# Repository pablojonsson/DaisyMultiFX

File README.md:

# Author
Pablo Jonsson

# DaisyMultiFX
Code for a Daisy Seed development board to run guitar effects

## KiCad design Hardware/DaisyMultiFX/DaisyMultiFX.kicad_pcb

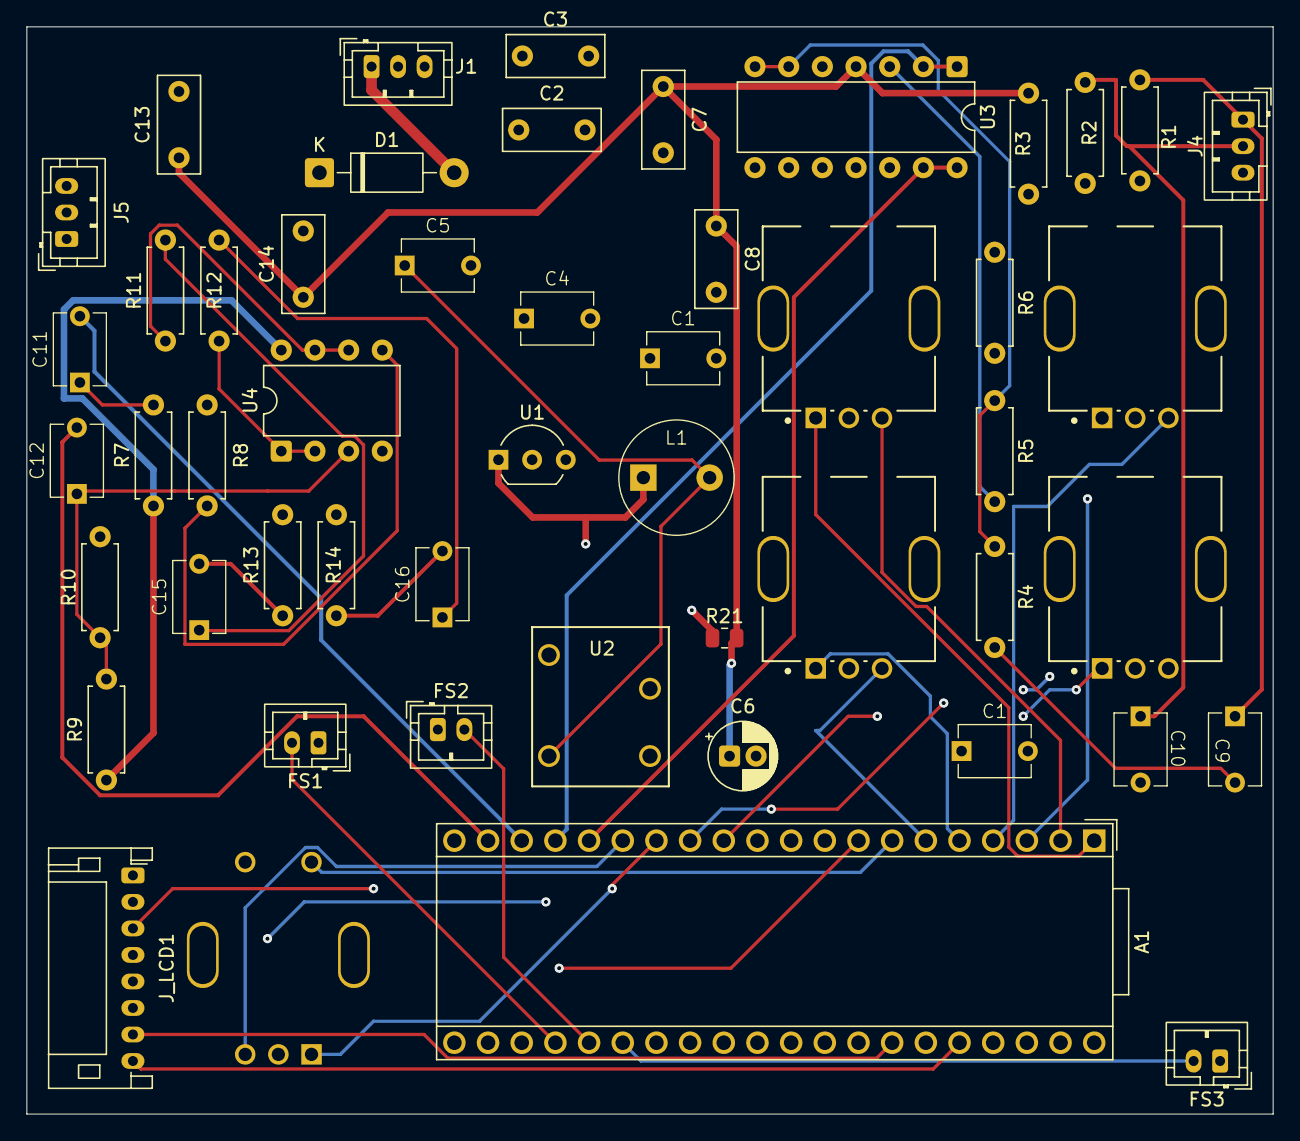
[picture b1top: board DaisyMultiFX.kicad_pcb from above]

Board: 4 copper layers, 94.0 x 82.0 mm, 51 parts (0 on the bottom side), 46 nets.

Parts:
A1: Electrosmith_Daisy_Seed_Rev4; Electrosmith_Daisy_Seed
C1, C1#2, C4, C5, C9, C10, C11, C12, C15, C16: 10UF; C_TDK_FG20_L5.5mm_T4.0mm_P5.00mm
C2, C3, C7, C8, C13, C14: 100NF; C_Rect_L7.2mm_W3.0mm_P5.00mm_FKS2_FKP2_MKS2_MKP2
C6: 22UF; CP_Radial_D5.0mm_P2.00mm
D1: 1N5817; D_DO-41_SOD81_P10.16mm_Horizontal
FS1: Foot_Switch_1; JST_PH_B2B-PH-K_1x02_P2.00mm_Vertical
FS2: Foot_Switch_2; JST_PH_B2B-PH-K_1x02_P2.00mm_Vertical
FS3: Foot_Switch_3; JST_PH_B2B-PH-K_1x02_P2.00mm_Vertical
J1: DC JACK; JST_PH_B3B-PH-K_1x03_P2.00mm_Vertical
J4: J_AUDIO_IN; JST_PH_B3B-PH-K_1x03_P2.00mm_Vertical
J5: J_AUDIO_OUT; JST_PH_B3B-PH-K_1x03_P2.00mm_Vertical
J_LCD1: WAVESHARE 2" ST7789PH2.0 8-pin; JST_PH_S8B-PH-K_1x08_P2.00mm_Horizontal
L1: 2.2uH; L_Bourns_RLB0912_D8.7mm_P5.00mm
R1, R2, R4, R5, R7, R8, R9, R10, R13, R14: 2M; R_Axial_DIN0207_L6.3mm_D2.5mm_P7.62mm_Horizontal
R3, R6: 100K; R_Axial_DIN0207_L6.3mm_D2.5mm_P7.62mm_Horizontal
R11, R12: 100R; R_Axial_DIN0207_L6.3mm_D2.5mm_P7.62mm_Horizontal
R21: DNP; R_0805_2012Metric
SW1, SW2, SW3, SW4: Encoder; Bourns-PEC11R-4220F-N0024-0-0-0
SW7: RotaryEncoder_Switch; Bourns-PEC11R-4220F-S0024-0-0-0
U1: L4931CZ50; TO-92_Inline_Wide
U2: NME0505DC; NME_DIP_MUR
U3: MCP6004; DIP-14_W7.62mm
U4: OPA2134; DIP-8_W7.62mm

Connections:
+3.3V: A1.38 (3V3_D), J_LCD1.1
+5V: C4.1, L1.1, R21.1, U1.1 (VO)
+5V_ISOLATED_POWER: C6.1, C7.1, C8.1, C13.1, C14.1, R3.1, R7.1, R9.1, R21.2, U2.5 (+VOUT), U3.4 (V+), U4.8 (V+)
+9V: A1.39 (VIN), C1.1, C1#2.1, C2.1, C3.1, D1.1 (K), U1.3 (VI)
/InputBuffer/V_AUDIOBIAS: R4.1, R5.1, U3.6 (-), U3.7
/Power/VIN: C5.1, L1.2, U2.4 (+VIN)
AUDIO_IN_BUFFER_LEFT: A1.16 (AUDIO_IN_1), U3.13 (-), U3.14
AUDIO_IN_BUFFER_RIGHT: A1.17 (AUDIO_IN_2), U3.1, U3.2 (-)
AUDIO_IN_JACK_LEFT: C9.1, J4.1, R1.1
AUDIO_IN_JACK_RIGHT: C10.1, J4.2, R2.1
AUDIO_OUT_BUFFER_LEFT: A1.18 (AUDIO_OUT_1), C11.2
AUDIO_OUT_BUFFER_RIGHT: A1.19 (AUDIO_OUT_2), C12.2
AUDIO_OUT_JACK_LEFT: C15.2, J5.1, R13.1
AUDIO_OUT_JACK_RIGHT: C16.2, J5.2, R14.1
ENC_1_A: A1.1 (USB_ID), SW1.A
ENC_1_B: A1.2 (SD_DATA_3), SW1.B
ENC_2_A: A1.3 (SD_DATA_2), SW2.A
ENC_2_B: A1.4 (SD_DATA_1), SW2.B
ENC_3_A: A1.5 (SD_DATA_0), SW3.A
ENC_3_B: A1.6 (SD_CMD), SW3.B
ENC_4_A: A1.12 (I2C1_SCL), SW4.A
ENC_4_B: A1.13 (I2C1_SDA), SW4.B
ENC_MASTER_A: A1.14 (USART1_TX), SW7.A
ENC_MASTER_B: A1.15 (USART1_RX), SW7.B
ENC_MASTER_SW: A1.7 (SD_CLK), SW7.1
FOOT_SWITCH_1: A1.24 (ADC_2), FS1.2
FOOT_SWITCH_2: A1.25 (ADC_3), FS2.2
FOOT_SWITCH_3: A1.26 (ADC_4), FS3.2
GND: A1.20 (AGND), A1.40 (DGND), C1.2, C1#2.2, C2.2, C3.2, C4.2, C5.2, C6.2, C7.2, C8.2, C13.2, C14.2, FS1.1, FS2.1, FS3.1, J1.2, J1.3, J4.3, J5.3, J_LCD1.2, R1.2, R2.2, R6.2, R8.2, R10.2, R13.2, R14.2, SW1.C, SW2.C, SW3.C, SW4.C, SW7.2, SW7.C, U1.2 (GND), U2.1 (-VIN), U2.7 (-VOUT), U3.10 (+), U3.11 (V-), U4.4 (V-)
LCD_BL: A1.36 (USB_D_-), J_LCD1.8
LCD_CS: A1.8 (SPI1_CS), J_LCD1.5
LCD_DC: A1.33 (SAI2_SD_A), J_LCD1.6
LCD_MOSI: A1.11 (SPI1_PICO), J_LCD1.3
LCD_RST: A1.34 (SAI2_FS), J_LCD1.7
LCD_SCK: A1.9 (SPI1_SCK), J_LCD1.4
unnamed: C15.1, R11.2
unnamed: C16.1, R12.2
unnamed: C10.2, R5.2, U3.3 (+)
unnamed: R3.2, R6.1, U3.5 (+)
unnamed: U3.8, U3.9 (-)
unnamed: C9.2, R4.2, U3.12 (+)
unnamed: C12.1, R9.2, R10.1, U4.3 (+)
unnamed: R12.1, U4.1, U4.2 (-)
unnamed: C11.1, R7.2, R8.1, U4.5 (+)
unnamed: R11.1, U4.6 (-), U4.7
POWER_JACK_PWR: D1.2 (A), J1.1
